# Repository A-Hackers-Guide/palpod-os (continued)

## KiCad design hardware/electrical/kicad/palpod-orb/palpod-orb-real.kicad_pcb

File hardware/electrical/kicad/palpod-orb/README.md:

# Hearth Orb — KiCad Project

Internal PCB for the 7-inch magnetically-levitating OLED sphere ("orb"): a
Nordic nRF54H20 dual-core Cortex-M33+M0 SoC coordinates 6× Sony IMX415 cameras
(via a Toshiba TC358748 MIPI CSI-2 aggregator), a ST VL53L8 depth sensor, a
Slamtec RPLIDAR S3, and a Qualcomm FC7800 Wi-Fi 7 module on an M.2 2230 Key
A+E socket. Wireless power comes in through a Renesas P9418 Qi RX and a
rectifier/LDO chain to 5V/3V3/1V8/1V2 rails, backed by a small Li-Po via a
TI BQ25798 buck-boost charger. Four TDK TMR2305 magnetoresistive sensors feed
the Halbach position loop back to the levitation controller in the column.
A Solomon Systech SSD1963 sits on a second rigid island as the placeholder
curved-OLED source driver and fans out over a 40-pin FPC to the panel.

The board is a **6-layer flex-rigid**: two rigid FR4 islands (one for the
main compute, one for the OLED driver) connected by polyimide flex bridges
that curl inside the sphere. See `../block-diagrams/orb.md` for the block
diagram and the mechanical/power/wireless budgets — this project is the
KiCad implementation.

## How to open

Requires **KiCad 8.0.0 or later** (KiCad 9 and 10 also open the files
cleanly; developed and validated against KiCad 10.0.5 on macOS).

```
open -a KiCad /private/tmp/claude-501/-Users-lexer-kindle/80e67baf-6192-4db2-b491-aa5b4ee00c5b/scratchpad/palpod-os/hardware/electrical/kicad/palpod-orb/palpod-orb.kicad_pro
```

Or double-click `palpod-orb.kicad_pro` in Finder. From the project manager,
open **Schematic Editor** and **PCB Editor**.

The project defines its own project-local symbol and footprint libraries in
`libraries/`; the `sym-lib-table` and `fp-lib-table` files at the project
root register them under the alias `palpod-orb`. Standard KiCad symbols
(`Device:R`, `Device:C`, `Device:L`, `Device:D_Schottky`,
`power:+5V/+3V3/+1V8/+1V2/+BATT/VRECT/GND`) are embedded in the schematic's
`lib_symbols` block so the schematic opens even on a fresh KiCad install
that has not yet been pointed at its stock libraries.

## What's populated

- [x] `.kicad_pro` project settings: 6-layer flex-rigid friendly minimums
      (0.09 mm min track / 0.3 mm min via for the CSI routing), net classes
      for `Default`, `Power`, `MIPI_CSI` (90 Ω differential, 0.1 mm),
      `MIPI_DSI`, `RF_50`, `FLEX`, `QI_RX`, auto-assign patterns for
      `+5V/+3V3/+1V8/+1V2/+BATT/VRECT`, `CAM?_D?_*`, `DSI_*`, `ANT_*/RF_*`,
      `COIL_AC*`.
- [x] `.kicad_sch` root schematic on A2, populated title block
      (rev A0, 2026-08-03), embedded `lib_symbols` for every reference
      (including all specialty ICs), 32 placed symbols.
- [x] Placed symbols: nRF54H20 (U1), TC358748 MIPI aggregator (U2),
      VL53L8 ToF (U3), BQ25798 BMS (U4), P9418 Qi RX (U5), SSD1963 OLED
      driver (U6), 4× TMR2305 Halbach sensors (U7..U10), 6× 28-pin FPC
      camera connectors (J1..J6, one per IMX415), Slamtec S3 LIDAR
      connector (J7), M.2 2230 Wi-Fi 7 socket (J8), 40-pin OLED FPC out
      (J9), 12× 100 nF decoupling caps, 4× 10 µF bulk caps, 2× 4.7 kΩ
      I²C pullups, 4× Schottky rectifier diodes (D1..D4), boost inductor
      (L1), VRECT bulk (C24), BATT bulk (C25). Power symbols for
      `+5V/+3V3/+1V8/+1V2/+BATT/VRECT/GND` (12 flags).
- [x] Illustrative wires and net labels on the power rails and the I²C
      bus, plus text labels seeding the MIPI CSI, MIPI DSI, Wi-Fi UART,
      and LIDAR UART buses.
- [x] `no_connect` flags on the two nRF54H20 antenna pins (ANT1/ANT2)
      since the RF path goes through the M.2 module in this design.
- [x] `libraries/palpod-orb.kicad_sym` — hand-drawn symbols for
      **all 11 specialty parts**: nRF54H20 (aQFN94), TC358748 (BGA80),
      SSD1963 (LFBGA121), Slamtec_S3 (10-pin conn), P9418 (QFN40),
      TMR2305 (SOT-23-5), VL53L8 (LGA16), CAM_FPC28 (28-pin ZIF for the
      IMX415), BQ25798 (QFN29), M2_2230_KeyAE (75-pin socket), OLED_FPC40
      (40-pin ZIF for curved OLED). **All pin groupings are placeholder;
      the EE must verify every ball/pad/pin number against the
      manufacturer datasheet before wiring.**
- [x] `libraries/palpod-orb.pretty/` — 11 placeholder footprints (see
      `libraries/palpod-orb.pretty/README.md` for the details and
      per-part verification checklist).
- [x] `.kicad_pcb` — **6-layer flex-rigid stackup declared** using KiCad
      8's stackup features: F.Cu / In1.Cu (GND) / In2.Cu (PWR_3V3) /
      In3.Cu (PWR_5V) / In4.Cu (GND) / B.Cu, with alternating FR4
      prepreg (rigid sections) and polyimide core (flex sections),
      1 oz outer / 0.5 oz inner effective, 1.05 mm nominal total,
      ENIG finish, dielectric constraints enabled.
- [x] **Board outline drawn as a single closed contour** covering both
      rigid islands + one flex bridge: rigid1 is 40×40 mm at the origin,
      rigid2 is 30×20 mm at x = 55..85, connected by a 35×15 mm flex
      neck at y = ±7.5. A second (return) flex bridge is called out on
      the `Dwgs.User` layer as documentation. `F.SilkS` labels on both
      islands and inside the flex neck. `Cmts.User` layer carries the
      6L stackup summary and the flex-rigid fab recommendation.
- [x] `sym-lib-table` / `fp-lib-table` register the project-local
      `palpod-orb` library. Standard KiCad libraries resolve from the
      user's install.

## What's stubbed / next steps for the EE

- [ ] **Verify placeholder footprints against real datasheets** before
      ordering fab. See `libraries/palpod-orb.pretty/README.md`. In
      particular:
    - nRF54H20 aQFN94 — replace with the Nordic vendor footprint
    - TC358748 BGA80 — regenerate from Toshiba's package outline
    - SSD1963 — **or swap in the real curved-OLED source driver footprint;
      SSD1963 is a placeholder for the proprietary vendor driver in the spec**
    - M.2 2230 Key A+E socket — replace with the actual Amphenol / Molex /
      TE socket footprint (with correct keying notch and dual-row edge pads)
    - Camera and OLED FPCs — pick the exact Molex / JST part first
- [ ] **Verify every specialty-symbol pin mapping** against the manufacturer
      datasheet. Ball/pad/pin numbers on the nRF54H20, TC358748, SSD1963,
      P9418, BQ25798, and M.2 socket symbols are placeholder groupings.
- [ ] Complete the schematic wiring:
    - MIPI CSI-2 fan-in: 6× 4-lane MIPI (24 diff pairs total) from J1..J6
      into TC358748's per-camera input banks. Length-match within each
      lane group per MIPI D-PHY skew budget (~0.05 mm).
    - MIPI CSI-2 fan-out: 4-lane CSI-2 from TC358748 to nRF54H20 (or to a
      LatticeSemi CrossLink NX FPGA if the EE chooses the FPGA aggregator
      option). This is the highest-speed bus on the board.
    - MIPI DSI: 4-lane DSI from either nRF54H20 (if it has DSI IP) or the
      SSD1963 host bus over to the OLED FPC (J9).
    - Wi-Fi 7 M.2 socket (J8) UART/SDIO/PCIe bringup to nRF54H20; drive
      `W_DISABLE`, `PERST_N`, and `WAKE_N` from MCU GPIOs.
    - LIDAR UART + motor PWM from J7 to nRF54H20 UART/PWM peripherals.
    - 4× TMR2305 Halbach sensors (U7..U10) → nRF54H20 SPI or ADC (choose
      one). If ADC, add anti-alias RC filters per the TMR2305 datasheet.
    - VL53L8 depth cam (U3) → nRF54H20 I²C + interrupt.
    - Qi RX power tree: coil pigtail → P9418 (U5) → Schottky rectifier
      (D1..D4) → C24 bulk → BQ25798 (U4) → SYS rail; SYS → LDO chain
      to +3V3 / +1V8 / +1V2. Battery on BQ25798's BAT pin with a Li-Po
      protection FET; C25 as VBAT bulk.
    - I²C bridge: nRF54H20 ↔ TC358748, VL53L8, P9418, BQ25798, camera EEPROMs,
      OLED touch. Add 4.7 kΩ pullups (R1, R2 already placed).
    - Reset/boot-strap sequencing: nRF54H20 GPIOs drive `RESET_N` on the
      cameras and the OLED driver, and hold `LPn` low on VL53L8 during
      power-up.
    - ESD protection on the USB pair inside the M.2 socket (TPD4S014) and
      on the LIDAR UART lines (TPD1E10B06).
    - SWD debug header (4-pin 1.27 mm) breaking out SWDIO / SWCLK / GND /
      VCC from nRF54H20.
- [ ] Run ERC (`kicad-cli sch erc palpod-orb.kicad_sch` or Tools →
      Electrical Rules Checker). The current stub reports ~1100
      violations, all consequences of the unwired stubs; drive them to
      zero.
- [ ] Assign every schematic symbol a valid footprint
      (Tools → Assign Footprints). Most already have footprints assigned;
      confirm the passives are on the correct 0402/0805/1210 sizes for
      the flex sections.
- [ ] Update the PCB from the schematic (Tools → Update PCB from
      Schematic in the PCB editor).
- [ ] Place footprints on the PCB:
    - **Rigid 1 (40×40 mm):** nRF54H20 in the center, TC358748 to the
      right of the MCU, VL53L8 near the top edge, BQ25798 near the
      power-input edge, P9418 next to the coil pigtail, 4× TMR2305 on
      the ring near the sphere's equatorial magnets, 6× camera FPC
      connectors around the perimeter, M.2 Wi-Fi socket along one full
      edge.
    - **Flex bridge:** route only the MIPI DSI 4 pairs + I²C + reset
      lines across the neck. 0.5 oz Cu, min bend radius = 6× flex
      thickness. Add a stiffener on B.Adhes at each rigid interface.
    - **Rigid 2 (30×20 mm):** SSD1963 (or the real OLED driver) in the
      center, OLED FPC (J9) along the right edge, decoupling caps
      immediately adjacent to VDD balls.
    - See `../block-diagrams/orb.md` for mass-budget / center-of-mass
      constraints (500 g total, CoM within 2 mm of geometric center).
- [ ] Route MIPI CSI-2 pairs first: 24 differential pairs (6 cameras ×
      4 lanes) into TC358748. Use the `MIPI_CSI` net class (90 Ω diff,
      0.1 mm trace on inner layer with GND reference). Length-match
      per-camera lane groups within 0.05 mm intra-pair and 0.5 mm
      inter-pair.
- [ ] Route MIPI DSI (4 lanes) from OLED driver to the panel FPC.
      Use `MIPI_DSI` net class.
- [ ] Pour GND on In1.Cu and In4.Cu (both GND layers). Split power on
      In2.Cu (3V3 zones) and In3.Cu (5V + VBAT + VRECT zones). Keep the
      Qi RX section GND on its own island, joined to the main GND only
      at the BQ25798 star point.
- [ ] Run DRC to zero. Current DRC reports 0 violations on the
      un-populated stub board.
- [ ] Generate Gerbers + drill + BOM + pick-and-place
      (`File → Fabrication Outputs`). Cross-check the BOM against
      `../block-diagrams/orb.md` §Block diagram.
- [ ] **Order proto run from a fab that supports flex-rigid.** This is
      **not** a JLCPCB / OSH Park capability at the standard tier —
      recommend **PCBWay Advanced (flex-rigid), MicroConnex, or Flex
      Interconnect** for the 6L polyimide-core stackup. Expect 4-6 week
      turn and a $5-15k NRE for the first article.

## Command-line validation

Validated with `kicad-cli` 10.0.5 (fontconfig warnings filtered):

```
kicad-cli sym export svg -o /tmp/orb-sym-svg libraries/palpod-orb.kicad_sym
# → renders all 11 specialty symbols to SVG

kicad-cli fp export svg -o /tmp/orb-fp-svg libraries/palpod-orb.pretty
# → renders all 11 placeholder footprints to SVG

kicad-cli sch export netlist -o /tmp/orb.net palpod-orb.kicad_sch
# → succeeds; produces 228 KB netlist covering all 32 placed symbols

kicad-cli sch erc palpod-orb.kicad_sch --output /tmp/orb-erc.rpt
# → Found 1100 violations (all unwired-stub consequences; expected)

kicad-cli pcb drc palpod-orb.kicad_pcb --output /tmp/orb-drc.rpt
# → Found 0 violations, 0 unconnected pads

kicad-cli pcb export gerbers -o fab/gerbers palpod-orb.kicad_pcb
kicad-cli pcb export drill    -o fab/gerbers/ palpod-orb.kicad_pcb
kicad-cli pcb export pdf      -o fab/palpod-orb-pcb.pdf ...
kicad-cli sch export pdf      -o fab/palpod-orb-schematic.pdf palpod-orb.kicad_sch
kicad-cli sch export bom      -o fab/palpod-orb-bom.csv       palpod-orb.kicad_sch
```

The `fab/` directory holds a full first-cut export: Gerber set, drill file,
schematic PDF, PCB PDF, BOM CSV, and a zip package. Everything is
regeneratable; do not treat these outputs as authoritative until the
placeholder symbols/footprints and wiring have been verified.

## File format

- Schematic schema version `20231120` (KiCad 8)
- PCB schema version `20240108` (KiCad 8)
- Symbol library schema version `20231120`
- Footprint schema version `20240108`

Written so the same files load identically under KiCad 8, 9, and 10.

## Required KiCad libraries

Bundled with a stock KiCad 8+ install; no external download needed:

- `Device` (R, C, L, D_Schottky) — also embedded in the schematic for
  offline opening
- `power` (+5V, +3V3, +1V8, +1V2, +BATT, VRECT, GND) — also embedded

Everything else — the 11 specialty symbols and their placeholder
footprints — lives in the project-local `palpod-orb` library registered
by `sym-lib-table` / `fp-lib-table`.

## Reference

- **Block diagram, power budget, wireless link budget, mechanical
  constraints:** `../block-diagrams/orb.md`
- **Sister project (main column mic array):**
  `../palpod-mic-array/README.md`

## Notes on flex-rigid representation

KiCad 8 has *partial* flex-rigid support — the stackup editor accepts
`(type "core")` and `(type "prepreg")` entries with different materials
(FR4 vs polyimide), so the 6L stackup here declares two polyimide-core
layers to represent the flex sections, and the flex-zone extent is
called out on the `Dwgs.User` and `F.SilkS` layers. KiCad does *not*
have a first-class "flex zone" primitive in v8, so the fab package
must be accompanied by a separate mechanical drawing showing:

1. Where the flex sections start and end (fab-house-defined "rigid
   region" polygons).
2. Which copper layers exist in the flex vs the rigid region (typically
   only F.Cu, In2.Cu, In3.Cu, B.Cu carry through the flex; the two
   GND layers stop at the rigid boundary).
3. Coverlay openings (instead of solder mask) on the flex sections.
4. Stiffener locations at each rigid/flex transition.

Attach that drawing to the Gerber package when requesting a quote.

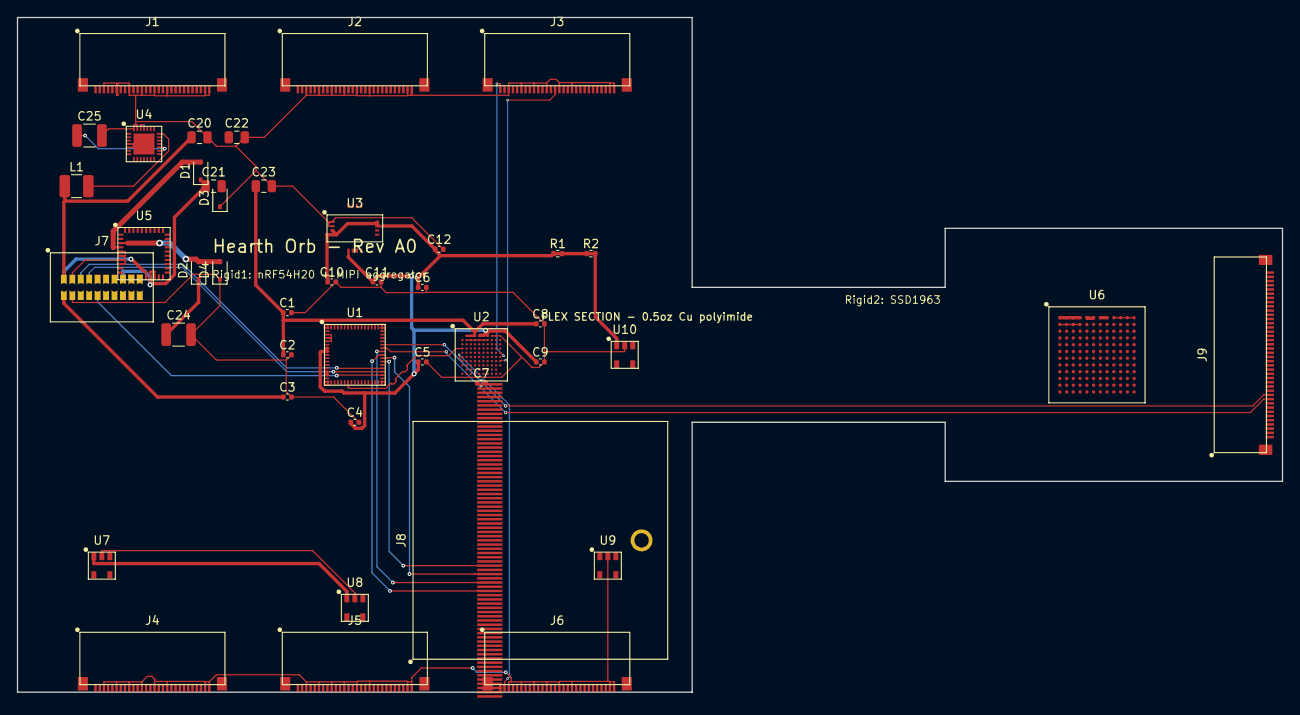
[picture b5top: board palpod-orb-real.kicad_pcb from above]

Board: 6 copper layers, 150.0 x 80.0 mm, 44 parts (0 on the bottom side), 64 nets.

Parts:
C1, C2, C3, C4, C5, C6, C7, C8, C9, C10, C11, C12: 100nF; C_0402_1005Metric
C20, C21, C22, C23: 10uF; C_0805_2012Metric
C24: 22uF; C_1210_3225Metric
C25: 220uF; C_1210_3225Metric
D1, D2, D3, D4: PMEG3020; D_SOD-323
J1: IMX415_CAM1; FPC28_0.5mm_ZIF
J2: IMX415_CAM2; FPC28_0.5mm_ZIF
J3: IMX415_CAM3; FPC28_0.5mm_ZIF
J4: IMX415_CAM4; FPC28_0.5mm_ZIF
J5: IMX415_CAM5; FPC28_0.5mm_ZIF
J6: IMX415_CAM6; FPC28_0.5mm_ZIF
J7: S3_LIDAR; S3_LIDAR_UART10
J8: WiFi7_M2; M2_2230_KeyAE
J9: OLED_OUT; FPC40_0.5mm_ZIF
L1: 10uH; L_1210_3225Metric
R1, R2: 4.7k; R_0402_1005Metric
U1: nRF54H20; nRF54H20_aQFN94
U2: TC358748; TC358748_BGA80
U3: VL53L8; VL53L8_LGA16
U4: BQ25798; BQ25798_QFN29
U5: P9418; P9418_QFN40
U6: SSD1963; SSD1963_LFBGA121
U7, U8, U9, U10: TMR2305; TMR2305_SOT23-5

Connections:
+1V2: C1.1, C2.1, C7.1, C8.1, C23.1, J1.26, J2.26, J3.26, J4.26, J5.26, J6.26, U1.1, U1.2, U1.3, U1.4, U1.5, U1.6, U2.A2, U2.A3, U2.A4
+1V8: C4.1, C5.1, C9.1, C11.1, C22.1, J1.25, J2.25, J3.25, J4.25, J5.25, J6.25, J9.24, U1.10, U1.11, U1.12, U1.13, U2.A5, U2.A6, U2.A7, U3.5, U6.A5, U6.A6
+3V3: C6.1, C10.1, C12.1, C21.1, J1.16, J1.17, J1.24, J2.16, J2.17, J2.24, J3.16, J3.17, J3.24, J4.16, J4.17, J4.24, J5.16, J5.17, J5.24, J6.16, J6.17, J6.24, J7.7, J7.8, J8.6, J8.8, J8.72, J8.74, J9.21, J9.22, J9.25, R1.1, R1.2, R2.1, R2.2, U1.59, U1.60, U3.1, U3.2, U3.9, U3.10, U4.7, U4.8, U5.17, U5.18, U6.A1, U6.A2, U6.A3, U6.A4, U7.1, U8.1, U9.1, U10.1
+5V: C3.1, C20.1, J7.1, L1.1, U1.7, U1.8, U1.9, U4.17, U4.18, U5.15, U5.16, U6.A7, U6.A8
+BATT: C25.1, U4.19, U4.20
BQ_REGN: U4.25, U4.26
BQ_SW1: L1.2, U4.15
CAM1_CLK_N: J1.13, U2.E4
CAM1_CLK_P: J1.14, U2.E3
CAM1_D0_N: J1.1, U2.E2
CAM1_D0_P: J1.2, U2.E1
CAM2_CLK_N: J2.13, U2.E8
CAM2_CLK_P: J2.14, U2.E7
CAM2_D0_N: J2.1, U2.E6
CAM2_D0_P: J2.2, U2.E5
CAM3_CLK_N: J3.13, U2.H6
CAM3_CLK_P: J3.14, U2.G10
CAM3_D0_N: J3.1, U2.E10
CAM3_D0_P: J3.2, U2.E9
CAM4_CLK_N: J4.13, U2.H7
CAM4_CLK_P: J4.14, U2.H1
CAM4_D0_N: J4.1, U2.G5
CAM4_D0_P: J4.2, U2.F9
CAM5_CLK_N: J5.13, U2.H8
CAM5_CLK_P: J5.14, U2.H2
CAM5_D0_N: J5.1, U2.G6
CAM5_D0_P: J5.2, U2.F10
CAM6_CLK_N: J6.13, U2.H9
CAM6_CLK_P: J6.14, U2.H3
CAM6_D0_N: J6.1, U2.G7
CAM6_D0_P: J6.2, U2.G1
COIL_AC1: D1.2, D3.2, U5.7
COIL_AC2: D2.2, D4.2, U5.8
CSI_CLK_N: U1.36, U2.D10
CSI_CLK_P: U1.35, U2.D9
CSI_D0_N: U1.28, U2.D2
CSI_D0_P: U1.27, U2.D1
CSI_D1_N: U1.30, U2.D4
CSI_D1_P: U1.29, U2.D3
CSI_D2_N: U1.32, U2.D6
CSI_D2_P: U1.31, U2.D5
CSI_D3_N: U1.34, U2.D8
CSI_D3_P: U1.33, U2.D7
DSI_CLK_N: J9.10, U1.46
DSI_CLK_P: J9.11, U1.45
DSI_D0_N: J9.4, U1.38
DSI_D0_P: J9.5, U1.37
DSI_D1_N: J9.7, U1.40
DSI_D1_P: J9.8, U1.39
DSI_D2_N: J9.13, U1.42
DSI_D2_P: J9.14, U1.41
DSI_D3_N: J9.16, U1.44
DSI_D3_P: J9.17, U1.43
GND: C1.2, C2.2, C3.2, C4.2, C5.2, C6.2, C7.2, C8.2, C9.2, C10.2, C11.2, C12.2, C20.2, C21.2, C22.2, C23.2, C24.2, C25.2, D3.1, D4.1, J1.3, J1.6, J1.9, J1.12, J1.15, J1.18, J1.27, J1.28, J2.3, J2.6, J2.9, J2.12, J2.15, J2.18, J2.27, J2.28, J3.3, J3.6, J3.9, J3.12, J3.15, J3.18, J3.27, J3.28, J4.3, J4.6, J4.9, J4.12, J4.15, J4.18, J4.27, J4.28, J5.3, J5.6, J5.9, J5.12, J5.15, J5.18, J5.27, J5.28, J6.3, J6.6, J6.9, J6.12, J6.15, J6.18, J6.27, J6.28, J7.2, J8.1, J8.2, J8.3, J8.4, J9.3, J9.6, J9.9, J9.12, J9.15, J9.18, J9.28, J9.33, J9.38, U1.14, U1.15, U1.16, U1.17, U1.18, U1.19, U1.20, U1.21, U2.A8, U2.A9, U2.B2, U2.B3, U2.B4, U2.B5, U2.B6, U2.B7, U3.3, U3.4, U4.3, U4.4, U4.27, U4.28, U4.29, U5.3, U5.4, U5.5, U5.6, U6.A9, U6.A10, U6.A11, U6.A12, U6.B1, U6.B2, U6.B3, U6.B4, U7.2, U8.2, U9.2, U10.2
LIDAR_MOTOR_PWM: J7.5, U1.54
LIDAR_SYNC: J7.6, U1.55
LIDAR_UART_RX: J7.4, U1.53
LIDAR_UART_TX: J7.3, U1.52
VRECT: C24.1, D1.1, D2.1, U4.1, U4.2, U5.1, U5.2, U5.13, U5.14
WIFI_DISABLE1_N: J8.7, U1.51
WIFI_PERST_N: J8.32, U1.50
WIFI_UART_RX: J8.26, U1.48
WIFI_UART_TX: J8.28, U1.47
WIFI_WAKE_N: J8.30, U1.49

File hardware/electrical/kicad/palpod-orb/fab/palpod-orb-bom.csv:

"Refs","Value","Footprint","Qty","DNP"
"C1","100nF","Capacitor_SMD:C_0402_1005Metric","1",""
"C2","100nF","Capacitor_SMD:C_0402_1005Metric","1",""
"C3","100nF","Capacitor_SMD:C_0402_1005Metric","1",""
"C4","100nF","Capacitor_SMD:C_0402_1005Metric","1",""
"C5","100nF","Capacitor_SMD:C_0402_1005Metric","1",""
"C6","100nF","Capacitor_SMD:C_0402_1005Metric","1",""
"C7","100nF","Capacitor_SMD:C_0402_1005Metric","1",""
"C8","100nF","Capacitor_SMD:C_0402_1005Metric","1",""
"C9","100nF","Capacitor_SMD:C_0402_1005Metric","1",""
"C10","100nF","Capacitor_SMD:C_0402_1005Metric","1",""
"C11","100nF","Capacitor_SMD:C_0402_1005Metric","1",""
"C12","100nF","Capacitor_SMD:C_0402_1005Metric","1",""
"C20","10uF","Capacitor_SMD:C_0805_2012Metric","1",""
"C21","10uF","Capacitor_SMD:C_0805_2012Metric","1",""
"C22","10uF","Capacitor_SMD:C_0805_2012Metric","1",""
"C23","10uF","Capacitor_SMD:C_0805_2012Metric","1",""
"C24","22uF","Capacitor_SMD:C_1210_3225Metric","1",""
"C25","220uF","Capacitor_SMD:C_1210_3225Metric","1",""
"D1","PMEG3020","Diode_SMD:D_SOD-323","1",""
"D2","PMEG3020","Diode_SMD:D_SOD-323","1",""
"D3","PMEG3020","Diode_SMD:D_SOD-323","1",""
"D4","PMEG3020","Diode_SMD:D_SOD-323","1",""
"J1","IMX415_CAM1","palpod-orb:FPC28_0.5mm_ZIF","1",""
"J2","IMX415_CAM2","palpod-orb:FPC28_0.5mm_ZIF","1",""
"J3","IMX415_CAM3","palpod-orb:FPC28_0.5mm_ZIF","1",""
"J4","IMX415_CAM4","palpod-orb:FPC28_0.5mm_ZIF","1",""
"J5","IMX415_CAM5","palpod-orb:FPC28_0.5mm_ZIF","1",""
"J6","IMX415_CAM6","palpod-orb:FPC28_0.5mm_ZIF","1",""
"J7","S3_LIDAR","palpod-orb:S3_LIDAR_UART10","1",""
"J8","WiFi7_M2","palpod-orb:M2_2230_KeyAE","1",""
"J9","OLED_OUT","palpod-orb:FPC40_0.5mm_ZIF","1",""
"L1","10uH","Inductor_SMD:L_1210_3225Metric","1",""
"R1","4.7k","Resistor_SMD:R_0402_1005Metric","1",""
"R2","4.7k","Resistor_SMD:R_0402_1005Metric","1",""
"U1","nRF54H20","palpod-orb:nRF54H20_aQFN94","1",""
"U2","TC358748","palpod-orb:TC358748_BGA80","1",""
"U3","VL53L8","palpod-orb:VL53L8_LGA16","1",""
"U4","BQ25798","palpod-orb:BQ25798_QFN29","1",""
"U5","P9418","palpod-orb:P9418_QFN40","1",""
"U6","SSD1963","palpod-orb:SSD1963_LFBGA121","1",""
"U7","TMR2305","palpod-orb:TMR2305_SOT23-5","1",""
"U8","TMR2305","palpod-orb:TMR2305_SOT23-5","1",""
"U9","TMR2305","palpod-orb:TMR2305_SOT23-5","1",""
"U10","TMR2305","palpod-orb:TMR2305_SOT23-5","1",""
